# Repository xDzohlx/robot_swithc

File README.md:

# robot_swithc
Switch de encendido para robots de combate
Main solo tiene los archivos actualizados de PCB y esquematicos
Para el software estan en su branch especifica

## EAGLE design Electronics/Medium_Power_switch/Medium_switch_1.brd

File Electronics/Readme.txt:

En esta carpeta se encuentran los archivos de electronica

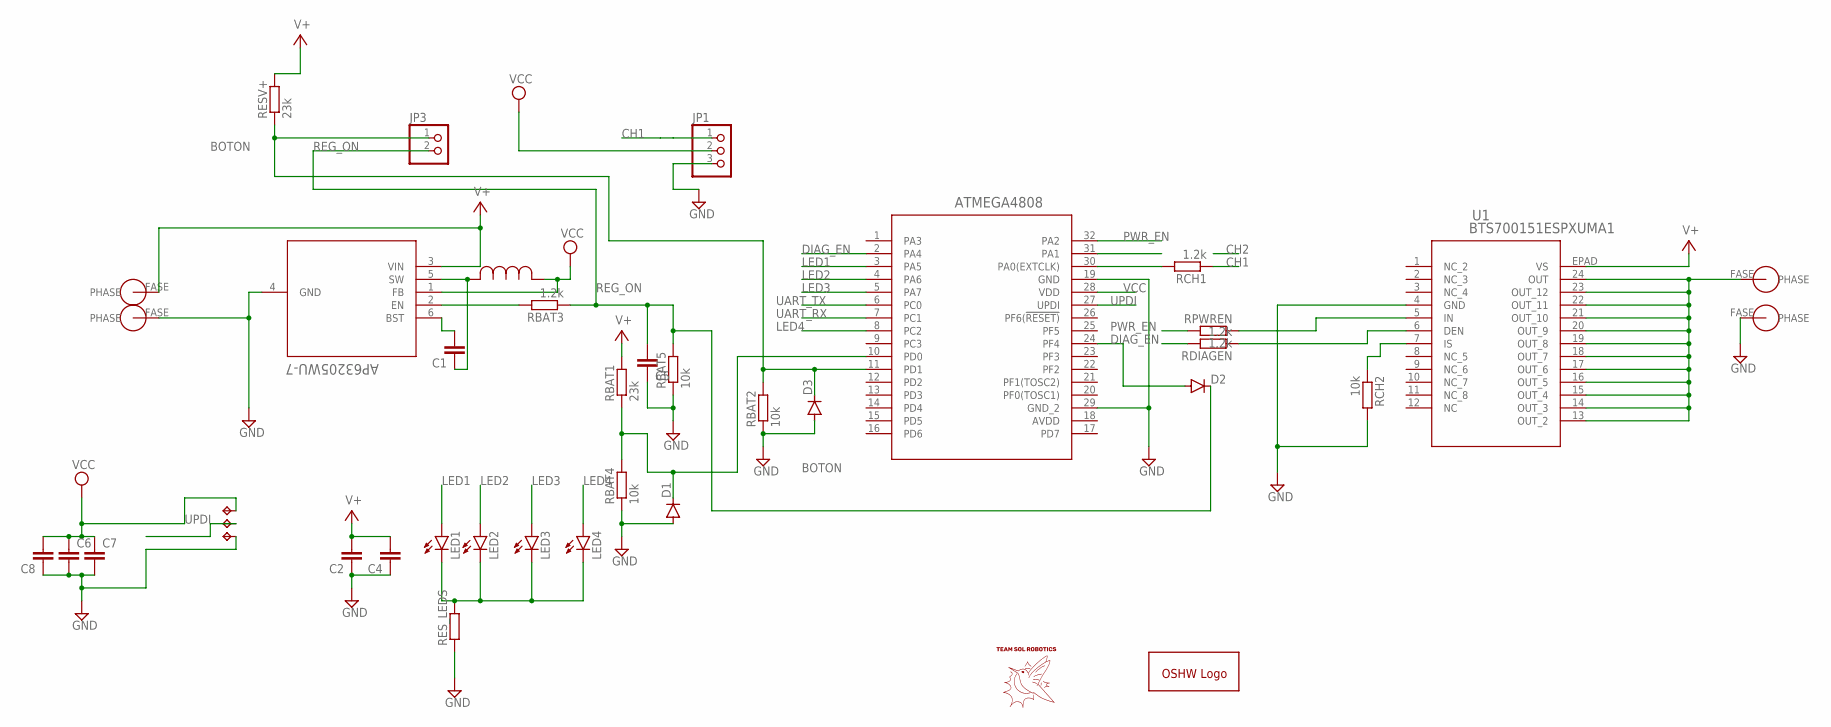
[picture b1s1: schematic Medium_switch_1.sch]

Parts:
BAT+: PHASE; POWEROUT
C1, C5, C8: C-EUC0402; C0402
C2, C4: C-EUC1206; C1206
C6, C7: C-EUC0805; C0805
D1, D3: DIODE-MICROMELF-R; MICROMELF-R
D2: DIODE-MINIMELF; MINIMELF
FASEA1, FASEA3: PHASE; POWEROUT
GOLD_ORB_SM1: OSHWLOGOLOGO5MM; OSHW_5MM
JP1: PINHD-1X03_2.54-S; 1X03-S
JP3: PINHD-1X02_2.00; 1X02M
LED1, LED2, LED3, LED4: LEDSML0603; SML0603
OUTPUTPWR: PHASE; POWEROUT
RBAT1: 23k; R0603
RBAT2, RBAT4, RBAT5: 10k; R0603
RBAT3: 1.2k; R0603
RCH1: 1.2k; R0603
RCH2: 10k; R0603
RDIAGEN: 1.2k; R0603
RESV+: 23k; R0603
RES_LEDS: R-EU_R0603; R0603
RPWREN: 1.2k; R0603
TP1, TP2, TP3: TPTP13SQ; TP13SQ
U1: BTS700151ESPXUMA1; PG-TSDSO-24-32
U2: AP63205WU-7; SOIC_05WU-7_DIO
U$1: ATMEGA4808; QFP80P900X900X120-32N
U$3: INDUCTOR4.7; IND_NRS5030T100MMGJ_TAY

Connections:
AVDD: U$1.18 (AVDD)
BOTON: D3.C, JP3.1, RBAT2.2, RESV+.1, U$1.11 (PD1)
CH1: JP1.1, RCH1.1
DIAG_EN: RDIAGEN.2, U$1.2 (PA4)
GND: C2.1, C4.1, C5.1, C6.2, C7.2, C8.1, D1.A, D3.A, FASEA1.FASE, FASEA3.FASE, JP1.3, RBAT2.1, RBAT4.1, RBAT5.1, RCH2.2, RES_LEDS.1, TP2.TP, U1.4 (GND), U2.4 (GND), U$1.19 (GND), U$1.29 (GND_2)
LED1: LED1.A, U$1.3 (PA5)
LED2: LED2.A, U$1.4 (PA6)
LED3: LED3.A, U$1.5 (PA7)
LED4: LED4.A, U$1.8 (PC2)
unnamed: RBAT3.2, U2.2 (EN)
unnamed: LED1.C, LED2.C, LED3.C, LED4.C, RES_LEDS.2
unnamed: RCH1.2, U$1.30 (PA0(EXTCLK))
unnamed: D2.A, U$1.24 (PF4)
unnamed: C1.1, U2.5 (SW), U$3.2
unnamed: RPWREN.1, U1.5 (IN)
unnamed: C1.2, U2.6 (BST)
unnamed: RDIAGEN.1, U1.6 (DEN)
unnamed: OUTPUTPWR.FASE, U1.13 (OUT_2), U1.14 (OUT_3), U1.15 (OUT_4), U1.16 (OUT_5), U1.17 (OUT_6), U1.18 (OUT_7), U1.19 (OUT_8), U1.20 (OUT_9), U1.21 (OUT_10), U1.22 (OUT_11), U1.23 (OUT_12), U1.24 (OUT)
unnamed: D1.C, RBAT1.1, RBAT4.2, U$1.10 (PD0)
unnamed: RCH2.1, U1.7 (IS)
PWR_EN: RPWREN.2, U$1.32 (PA2)
REG_ON: C5.2, D2.C, JP3.2, RBAT3.1, RBAT5.2
UART_RX: U$1.7 (PC1)
UART_TX: U$1.6 (PC0)
UPDI: TP3.TP, U$1.27 (UPDI)
V+: BAT+.FASE, C2.2, C4.2, RBAT1.2, RESV+.2, U1.EPAD (VS), U2.3 (VIN)
VCC: C6.1, C7.1, C8.2, JP1.2, TP1.TP, U2.1 (FB), U$1.28 (VDD), U$3.1

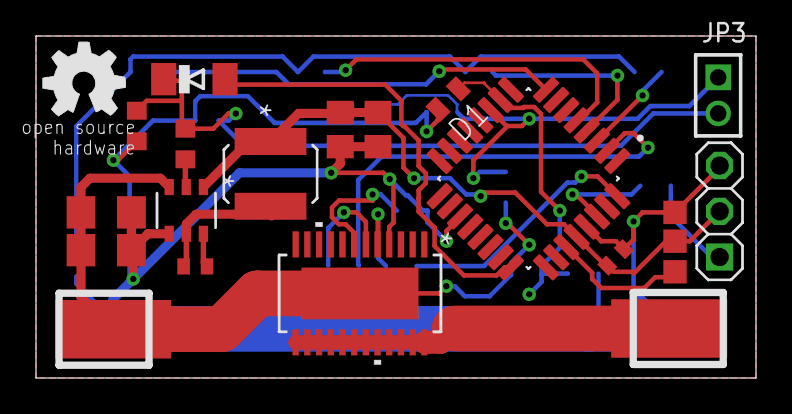
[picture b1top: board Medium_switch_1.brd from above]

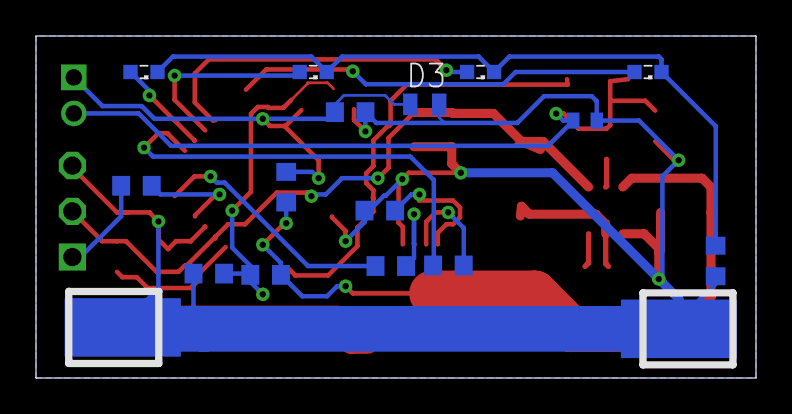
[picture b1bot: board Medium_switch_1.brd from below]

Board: 2 copper layers, 40.0 x 19.0 mm, 39 parts (17 on the bottom side), 24 nets.

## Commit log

2024-06-29 Firmware estable prende y apgaga
2024-06-29 PCB y esquematico
2024-06-29 Cambios menores
2024-07-15 Encendido y apagado estable con 4s
2024-08-14 Fix de boton
2024-08-15 Software estable BOD ON
2024-08-17 Stable version
2024-08-18 High load HSS, 130amp
2024-08-18 Nuevos esquematicos y PCB
2024-09-11 Create Lanzallamas.c
    Codigo actual de lanzallamas
2024-10-22 Dos HSS para bobina y resistencia

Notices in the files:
parts and their libraries:
COPYRIGHT: Copyright (C) 2018 Accelerated Designs. All rights reserved
COPYRIGHT: Copyright (C) 2023 Ultra Librarian. All rights reserved.
